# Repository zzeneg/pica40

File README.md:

# Pica40 v2

Split keyboard with 40 keys using XIAO controllers.

_Pica pica - european (common) magpie_

## Features

- 40 keys
- high profile (regular MX switches with hotswap sockets) or low profile (soldered low-profile ChocV2 switches)
- wired/wireless versions
- aggressive stagger
- slightly splayed for pinky columns

### Wired version

- XIAO RP2040 controller
- QMK firmware
- USB-C or TRRS connection between splits
- one rotary encoder (without click)
- status LED

### Wireless version

- XIAO nRF52840 BLE controller
- ZMK firmware
- two rotary encoders (without click, only master side encoder is currently supported by ZMK)
- on/off toggle
- battery connectors

> [!NOTE]
> I created a beta version with small improvements for wireless version - https://github.com/zzeneg/pica40/tree/v2.2-beta?tab=readme-ov-file#v22. I'm fairly confident it should work but I'm not able to verify it at the moment. You can order it at your own risk, let me know if everything worked.

## Photos

wired version with 3d printed case

wired/wireless versions with Choc V2

Pica40 family - ChocV2 with low profile keycaps, ChocV2 with MT3 keycaps, Pica40 v1 with MT3 keycaps, regular switches and hotswap sockets

## Firmware

- QMK - available in [main repository](https://github.com/qmk/qmk_firmware/tree/master/keyboards/pica40), also check [my fork](https://github.com/zzeneg/qmk_firmware/tree/feature/zzeneg/keyboards/pica40) for most recent updates. [Compiled file](firmware/qmk/pica40_rev2_zzeneg.uf2).
- Vial - [my fork](https://github.com/zzeneg/vial-qmk/tree/feature/zzeneg/keyboards/pica40). [Compiled file](firmware/vial/pica40_rev2_vial-zzeneg.uf2).
- ZMK - [Source code](https://github.com/zzeneg/zmk-config), [compiled left](firmware/zmk/pica40_left.uf2), [compiled right](firmware/zmk/pica40_right.uf2), [reset](firmware/zmk/settings_reset.uf2)

## Gerber files

- [PCB](./pcb/production/full.zip)
- [Bottom plate](./case/production/bottom.zip)

## Case files (STL - 3d printed, MX hotswap only)

All files are in [stl](./stl) folder.

### Top:

- wired/wireless versions
- with and without encoders
- normal and thin versions (see bottom parts for difference)

### Bottom:

Normal version - solid cover, cutouts for legs.
Thin version - 1.2mm lower than normal version, cutouts for all elements. Has additional cutouts for magnets.

Thin vs normal:

## Case files (DXF - for metal/acrylic)

- [Curved bottom for MX hotswap with 3D printed case](dxf/bottom-curved.dxf)
- [Bottom for soldered ChocV2](dxf/bottom.dxf)
- [MCU cover](dxf/cover.dxf)
- [MCU cover with encoder hole](dxf/cover-hole.dxf)

## Bill of materials

- PCBs
- 2 XIAO MCUs - [RP2040](https://www.seeedstudio.com/XIAO-RP2040-v1-0-p-5026.html) for wired version, [nRF52840](https://www.seeedstudio.com/Seeed-XIAO-BLE-nRF52840-p-5201.html) for wireless
- 40 SMD SOD-123 1N4148 diodes
- 1 or 2 EC11/12 rotary encoder with knob (diameter up to 20mm)
- _[MX hotswap version]_ 3d printed case (top and bottom, left and right - 4 files)
- _[MX hotswap version]_ 40 hotswap sockets
- _[MX hotswap version]_ [M2 standoffs](https://www.aliexpress.com/item/4001271908929.html) (4mm for thin, 5mm for normal), 3mm [M2 screws with flat head](https://www.aliexpress.com/item/4001248931159.html)
- _[MX hotswap thin version]_ [8x2mm magnets](https://www.aliexpress.com/item/1005002285176336.html) (optional)
- _[ChocV2 soldered version]_ FR4/metal/acrylic bottom plates, metal/acrylic MCU cover (optional)
- _[ChocV2 soldered version]_ 6mm M2 screws, M2 nuts and washers
- _[Wired only]_ [USB-C 16pin connectors](https://www.aliexpress.com/item/1005003670899595.html)
- _[Wired only]_ [TRRS PJ-320A connectors](https://www.aliexpress.com/item/1005001928651798.html)
- _[Wireless only]_ [2x on/off toggle MSK-12C02](https://www.aliexpress.com/item/4000685483225.html)
- _[Wireless only]_ 2x Li-Ion 3.7V battery (up to 25x14x5 for standard case)
- [7mm legs](https://www.aliexpress.com/item/1005002995402961.html) or [rubber sheet](https://www.aliexpress.com/item/1005003938672544.html) (recommended for thin version)

## Build log

**TODO**

## Development

For proper KiCad setup install my [zzkeeb](https://github.com/zzeneg/zzkeeb/blob/main/README.md#installation) library.

## Changelog

### V2.2

- improve XIAO BLE footprints for easier SMD-like soldering
- remove ground planes for better wireless performance

### V2.1

- added TRRS support
- wired version supports rotary encoder on any side
- remove unused for FR4/acrylic/metal sandwich case, 3D printing is better and cheaper
- improved 3D printed case with a new shape and parts

### V2

- reworked to true split with two XIAO MCUs controllers
- added splay to pinky columns
- all case/pcb files are not compatible with V1

### V1

- split with single Pro Micro based MCU and handwired connection

## Support

If you like my work and want to support my future designs, please consider [sponsorship](https://github.com/sponsors/zzeneg).

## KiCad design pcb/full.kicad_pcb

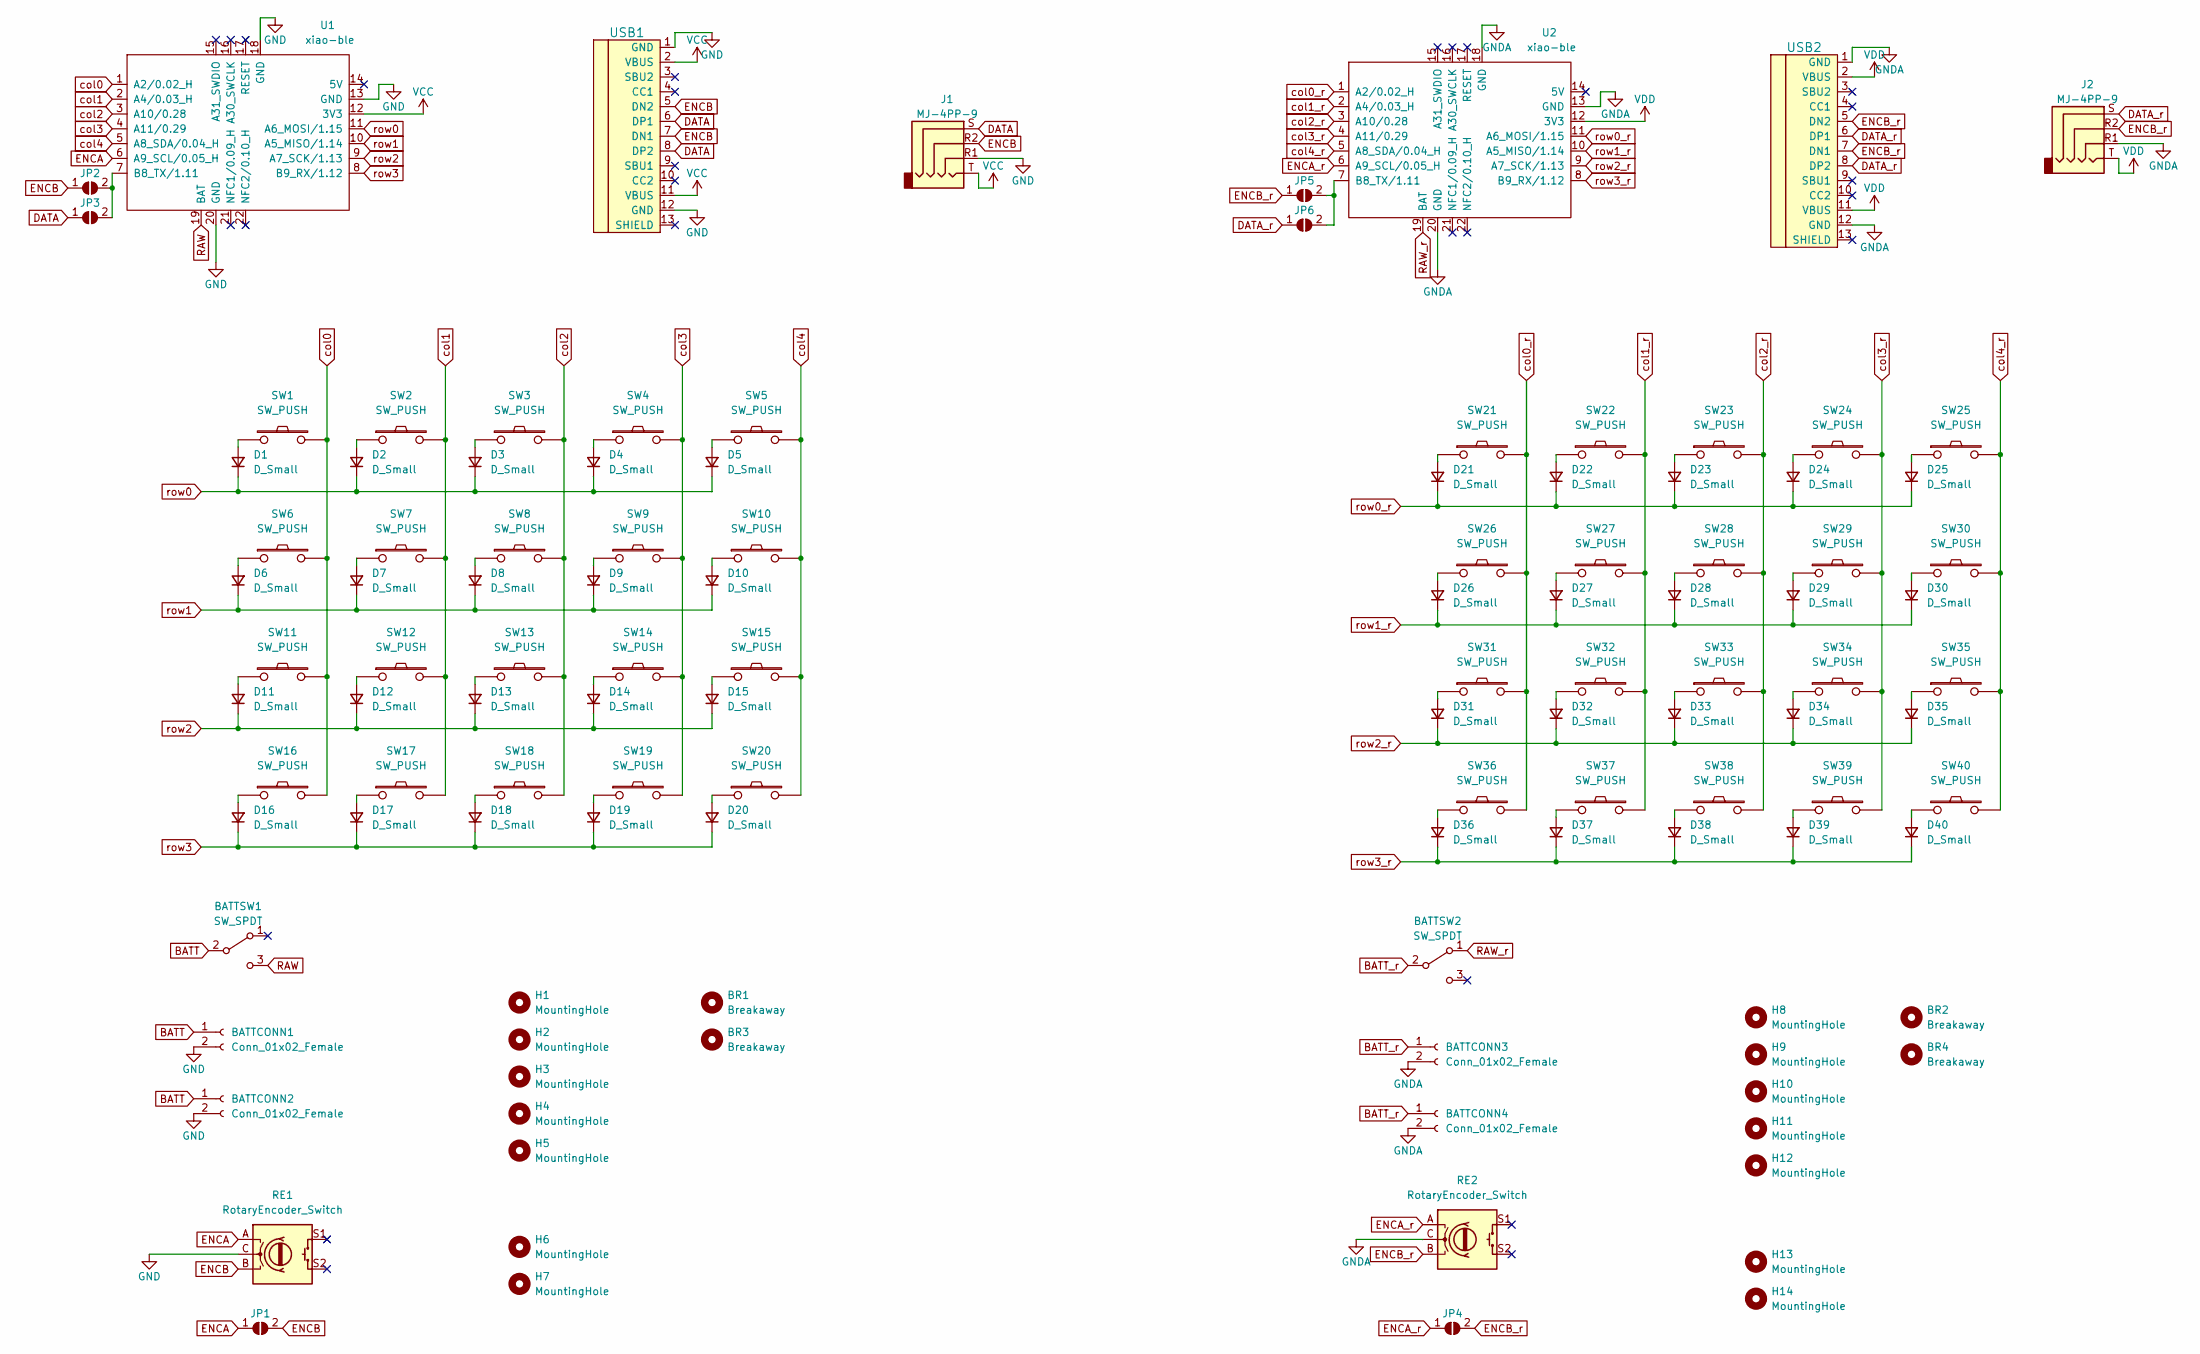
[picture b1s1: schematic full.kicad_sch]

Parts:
BATTCONN1, BATTCONN2, BATTCONN3, BATTCONN4: Conn_01x02_Female; Connector_JST-1x02-2.00mm
BATTSW1, BATTSW2: SW_SPDT; Switch_SPDT-PCM12
BR1, BR2, BR3, BR4: Breakaway; Hole_Breakaway-Tabs
D1, D2, D3, D4, D5, D6, D7, D8, D9, D10, D11, D12, D13, D14, D15, D16, D17, D18, D19, D20, D21, D22, D23, D24, D25, D26, D27, D28, D29, D30, D31, D32, D33, D34, D35, D36, D37, D38, D39, D40: D_Small; Diode_1N4148-SOD123-no-label
H1, H2, H3, H4, H5, H8, H9, H10, H11, H12: MountingHole; Hole_M2-spacer
H6, H7, H13, H14: MountingHole; Hole_M2
J1, J2: MJ-4PP-9; Connector_TRRS
JP1, JP2, JP3, JP4, JP5, JP6: SolderJumper_2_Open; SolderJumper-2_P1.3mm_Open_TrianglePad1.0x1.5mm
RE1, RE2: RotaryEncoder_Switch; RotaryEncoder_EC11
SW1, SW2, SW3, SW4, SW5, SW6, SW7, SW8, SW9, SW10, SW11, SW12, SW13, SW14, SW15, SW16, SW17, SW18, SW19, SW21, SW22, SW23, SW24, SW25, SW26, SW27, SW28, SW29, SW30, SW31, SW32, SW33, SW34, SW35, SW36, SW37, SW38, SW39: SW_PUSH; Switch_MXChocV2-hotswap
SW20, SW40: SW_PUSH; Switch_MXChocV2-hotswap-1.5
U1, U2: xiao-ble; MCU_xiao-ble-tht
USB1, USB2: HRO-TYPE-C-31-M-12; Connector_HRO-TYPE-C-31-M-12-data

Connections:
BATT: BATTCONN1.1, BATTCONN2.1, BATTSW1.2 (B)
BATT_r: BATTCONN3.1, BATTCONN4.1, BATTSW2.2 (B)
DATA: J1.S, JP3.1 (A), USB1.6 (DP1), USB1.8 (DP2)
DATA_r: J2.S, JP6.1 (A), USB2.6 (DP1), USB2.8 (DP2)
ENCA: JP1.1 (A), RE1.A, U1.6 (A9_SCL/0.05_H)
ENCA_r: JP4.1 (A), RE2.A, U2.6 (A9_SCL/0.05_H)
ENCB: J1.R2, JP1.2 (B), JP2.1 (A), RE1.B, USB1.5 (DN2), USB1.7 (DN1)
ENCB_r: J2.R2, JP4.2 (B), JP5.1 (A), RE2.B, USB2.5 (DN2), USB2.7 (DN1)
GND: BATTCONN1.2, BATTCONN2.2, J1.R1, RE1.C, U1.13 (GND), U1.18 (GND), U1.20 (GND), USB1.1 (GND), USB1.12 (GND)
GNDA: BATTCONN3.2, BATTCONN4.2, J2.R1, RE2.C, U2.13 (GND), U2.18 (GND), U2.20 (GND), USB2.1 (GND), USB2.12 (GND)
unnamed: D1.2 (A), SW1.1
unnamed: D2.2 (A), SW2.1
unnamed: D3.2 (A), SW3.1
unnamed: D4.2 (A), SW4.1
unnamed: D5.2 (A), SW5.1
unnamed: D6.2 (A), SW6.1
unnamed: D7.2 (A), SW7.1
unnamed: D8.2 (A), SW8.1
unnamed: D9.2 (A), SW9.1
unnamed: D10.2 (A), SW10.1
unnamed: D11.2 (A), SW11.1
unnamed: D12.2 (A), SW12.1
unnamed: D13.2 (A), SW13.1
unnamed: D14.2 (A), SW14.1
unnamed: D15.2 (A), SW15.1
unnamed: D16.2 (A), SW16.1
unnamed: D17.2 (A), SW17.1
unnamed: D18.2 (A), SW18.1
unnamed: D19.2 (A), SW19.1
unnamed: D20.2 (A), SW20.1
unnamed: D21.2 (A), SW21.1
unnamed: D22.2 (A), SW22.1
unnamed: D23.2 (A), SW23.1
unnamed: D24.2 (A), SW24.1
unnamed: D25.2 (A), SW25.1
unnamed: D26.2 (A), SW26.1
unnamed: D27.2 (A), SW27.1
unnamed: D28.2 (A), SW28.1
unnamed: D29.2 (A), SW29.1
unnamed: D30.2 (A), SW30.1
unnamed: D31.2 (A), SW31.1
unnamed: D32.2 (A), SW32.1
unnamed: D33.2 (A), SW33.1
unnamed: D34.2 (A), SW34.1
unnamed: D35.2 (A), SW35.1
unnamed: D36.2 (A), SW36.1
unnamed: D37.2 (A), SW37.1
unnamed: D38.2 (A), SW38.1
unnamed: D39.2 (A), SW39.1
unnamed: D40.2 (A), SW40.1
unnamed: JP2.2 (B), JP3.2 (B), U1.7 (B8_TX/1.11)
unnamed: JP5.2 (B), JP6.2 (B), U2.7 (B8_TX/1.11)
RAW: BATTSW1.3 (C), U1.19 (BAT)
RAW_r: BATTSW2.1 (A), U2.19 (BAT)
VCC: J1.T, U1.12 (3V3), USB1.2 (VBUS), USB1.11 (VBUS)
VDD: J2.T, U2.12 (3V3), USB2.2 (VBUS), USB2.11 (VBUS)
col0: SW1.2, SW6.2, SW11.2, SW16.2, U1.1 (A2/0.02_H)
col0_r: SW21.2, SW26.2, SW31.2, SW36.2, U2.1 (A2/0.02_H)
col1: SW2.2, SW7.2, SW12.2, SW17.2, U1.2 (A4/0.03_H)
col1_r: SW22.2, SW27.2, SW32.2, SW37.2, U2.2 (A4/0.03_H)
col2: SW3.2, SW8.2, SW13.2, SW18.2, U1.3 (A10/0.28)
col2_r: SW23.2, SW28.2, SW33.2, SW38.2, U2.3 (A10/0.28)
col3: SW4.2, SW9.2, SW14.2, SW19.2, U1.4 (A11/0.29)
col3_r: SW24.2, SW29.2, SW34.2, SW39.2, U2.4 (A11/0.29)
col4: SW5.2, SW10.2, SW15.2, SW20.2, U1.5 (A8_SDA/0.04_H)
col4_r: SW25.2, SW30.2, SW35.2, SW40.2, U2.5 (A8_SDA/0.04_H)
row0: D1.1 (K), D2.1 (K), D3.1 (K), D4.1 (K), D5.1 (K), U1.11 (A6_MOSI/1.15)
row0_r: D21.1 (K), D22.1 (K), D23.1 (K), D24.1 (K), D25.1 (K), U2.11 (A6_MOSI/1.15)
row1: D6.1 (K), D7.1 (K), D8.1 (K), D9.1 (K), D10.1 (K), U1.10 (A5_MISO/1.14)
row1_r: D26.1 (K), D27.1 (K), D28.1 (K), D29.1 (K), D30.1 (K), U2.10 (A5_MISO/1.14)
row2: D11.1 (K), D12.1 (K), D13.1 (K), D14.1 (K), D15.1 (K), U1.9 (A7_SCK/1.13)
row2_r: D31.1 (K), D32.1 (K), D33.1 (K), D34.1 (K), D35.1 (K), U2.9 (A7_SCK/1.13)
row3: D16.1 (K), D17.1 (K), D18.1 (K), D19.1 (K), D20.1 (K), U1.8 (B9_RX/1.12)
row3_r: D36.1 (K), D37.1 (K), D38.1 (K), D39.1 (K), D40.1 (K), U2.8 (B9_RX/1.12)

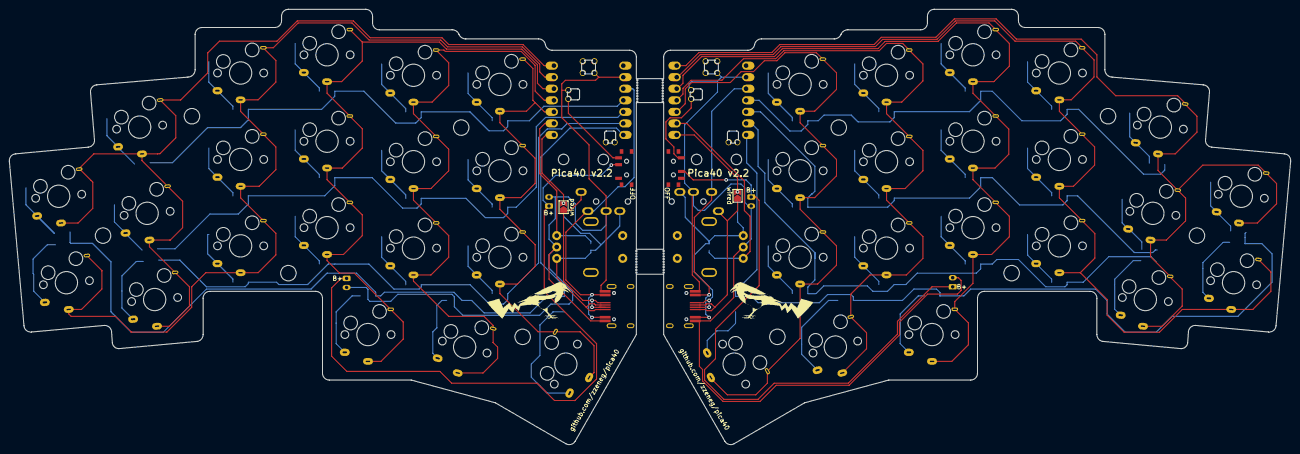
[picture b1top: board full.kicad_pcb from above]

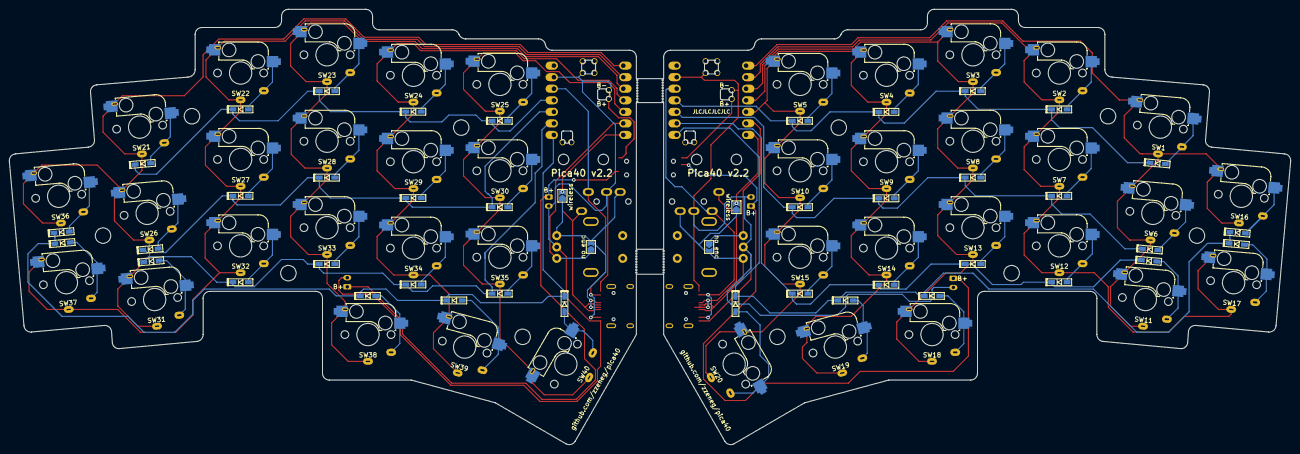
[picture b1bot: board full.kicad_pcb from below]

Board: 2 copper layers, 281.7 x 95.7 mm, 118 parts (51 on the bottom side), 74 nets.

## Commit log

2022-05-10 add libs
2022-05-12 add pcb
2022-05-12 plate/bottom
2022-05-12 update gerber
2022-05-13 fixes
2022-05-13 readme
2022-05-13 fix 3d model
2022-05-14 flip oled jumpers
2022-05-18 logos and jlcpcb texts
2022-05-24 add breakaway plate, replace battery connector
2022-05-24 move diodes
2022-05-25 generate dxf files
2022-05-25 fix gerbers
2022-05-25 add bottom-tenting, reorganize
2022-06-08 update breakaway design to satisfy jlcpcb
2022-06-09 update and reroute
2022-06-10 update case files
2022-06-12 remove logos from top
2022-06-12 use footprints with PTH slots
2022-06-13 separate plates
2022-06-13 Revert "use footprints with PTH slots"
    This reverts commit bdcc6b4fc5c42f5b6ab726123ea9fec0ebe93fb2.
2022-06-13 fix LED footprint
2022-06-13 separate left and right sides
2022-06-13 fix battery connector footprint
2022-06-14 update cases, extra hole on right side
2022-07-16 non-reversible pcbs
2022-07-16 improve rotary encoder footprint
2022-07-16 update 3d models and renders
2022-08-08 add kleeb lib
2022-08-11 add full version
2022-08-13 rounded traces
2022-09-14 remove second encoder
2022-09-22 update cover
2022-09-22 update bottom-tenting
2022-11-08 add big cover
2022-11-08 add firmware
2022-11-08 cover without hole
2022-11-10 adjust top plate, add new cover in PCB style
2022-11-11 fix DXF files for new covers
2022-11-15 remove small cover
2022-11-16 udpate pcb, remove unused files
2022-11-26 improve footprints and routing
2022-11-26 remove lib
2022-11-26 fix dxf files
2022-12-03 update firmware
2022-12-08 update readme and firmware files
2022-12-15 add top left/right/full case files
2022-12-20 add STLs
2022-12-21 add bottom cutout for chocs
2022-12-21 add bottom cutout
2022-12-23 remove zones from bottom to prevent shorting
2023-01-05 update case files, remove left/right files, update readme
2023-01-05 add stl for switch plate
2023-01-05 update pcb
2023-01-05 fix components and pcbs
2023-01-10 fix bottom cutout plates
2023-01-19 improve 3d printed cases
2023-02-16 migrate to my component library
2023-02-16 update 3d files
2023-02-16 fix ChocV2 footprint
2023-02-17 remove unsupported case files
2023-02-17 update bottom
2023-02-17 add pcb 3d
2023-02-18 add case files
2023-02-18 update pcb silkscreen
2023-02-20 fix images in readme
2023-02-20 add magnet holes, fix leg holes
2023-02-20 restore bottom files
2023-02-25 top-mount usb-c
2023-02-25 update cases
2023-03-09 small update for bottom case
2023-03-14 plot references
2023-03-21 small case updates
2023-03-21 restore cover files
2023-03-21 latest firmware
2023-04-14 new wireless case
2023-05-18 improve new wireless case
2023-09-27 restore hole for power switch in wireless cases
2023-09-30 fix battery cover thickness, add leg cutouts
2023-10-18 Revert "Update README.md"
    This reverts commit 7484fe026ea64984b656c1493c0ae8b3024599ce.
2023-11-20 fix mcu hole in battery case
2024-02-10 add tpu case
2024-02-11 v2.2
2024-04-10 update tpu case
2024-04-15 restructure
